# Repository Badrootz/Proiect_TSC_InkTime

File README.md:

# InkTime

## Overview

InkTime is a low-power smartwatch built around the Nordic nRF52840 SoC, designed for efficient operation, wireless connectivity, and a clean e-paper display interface. The project focuses on power optimization, modular hardware design, and practical embedded system integration.

---

## Block Diagram

```mermaid
graph TD
    Battery[LiPo Battery] --> PMIC[BQ25180 PMIC]
    PMIC --> VREG[3.3V Regulator]
    VREG --> MCU[nRF52840]

    MCU --> IMU[BMA421 IMU]
    MCU --> Display[E-Paper Display]
    MCU --> Haptic[DRV2605 Haptic Driver]
    MCU --> Fuel[MAX17048 Fuel Gauge]

    USB[USB-C] --> PMIC
    USB --> MCU

    MCU --> SWD[SWD Debug]
```

---

## Bill of Materials (BOM)

| Component      | Part Number   | Description          | Link (JLC) | Datasheet         |
| -------------- | ------------- | -------------------- | ---------- | ----------------- |
| MCU            | nRF52840-QFN  | BLE SoC              | JLC        | Nordic Datasheet  |
| PMIC           | BQ25180YBGR   | Charger + Power Path | JLC        | TI Datasheet      |
| IMU            | BMA421        | Accelerometer        | JLC        | Bosch Datasheet   |
| Fuel Gauge     | MAX17048G+T10 | Battery Monitor      | JLC        | Maxim Datasheet   |
| Haptic Driver  | DRV2605       | Vibration Driver     | JLC        | TI Datasheet      |
| Buck Converter | RT6160A       | Step-down regulator  | JLC        | Richtek Datasheet |
| USB Protection | USBLC6-2SC6   | ESD Protection       | JLC        | ST Datasheet      |
| Inductors      | Various       | Power filtering      | JLC        | Datasheets        |
| Capacitors     | Various       | Decoupling           | JLC        | Datasheets        |
| Resistors      | Various       | Pull-ups / config    | JLC        | Datasheets        |

---

## Hardware Functionality (Detailed)

### MCU (nRF52840)

Main processing unit. Handles:

* BLE communication
* Sensor data processing
* Display control
* Power management coordination

Runs at low power modes most of the time, wakes up on interrupts (IMU, buttons, timers).

---

### Power Management

#### BQ25180 PMIC

* Handles LiPo charging
* Power path management (system + battery)
* Integrated buck converter

#### RT6160 Buck Converter

* Steps voltage down efficiently to 3.3V
* Supplies MCU and peripherals

#### Power Design Notes

* Multiple decoupling capacitors placed close to ICs
* Separate analog and digital grounds where needed
* High-efficiency switching to maximize battery life

---

### IMU (BMA421)

* Connected via I2C
* Provides motion detection
* Generates interrupts for wake-up

Used for:

* Step detection
* Gesture-based wake

---

### E-Paper Display

* SPI communication
* Requires additional driving circuitry (boost + level shifting)
* Very low power (only consumes when refreshing)

Signals:

* MOSI, SCK (SPI)
* CS, DC, RST, BUSY (control)

---

### Fuel Gauge (MAX17048)

* Connected via I2C
* Monitors battery percentage
* Provides alerts when battery is low

---

### Haptic Driver (DRV2605)

* Controlled via I2C
* Drives vibration motor
* Used for notifications

---

### USB-C Interface

* Used for charging + debugging
* Includes ESD protection
* Connected to MCU USB pins

---

## nRF52840 Pin Usage

| Pin            | Function        | Reason                                   |
| -------------- | --------------- | ---------------------------------------- |
| P0.26 / P0.27  | I2C (SDA/SCL)   | Shared bus for IMU + Fuel Gauge + Haptic |
| P0.13 / P0.14  | USB D- / D+     | USB communication                        |
| P0.15 - P0.20  | SPI (Display)   | High-speed display communication         |
| P0.22 - P0.24  | Display Control | CS, DC, RST                              |
| P0.25          | Display BUSY    | Sync with display                        |
| P1.x           | GPIO            | Buttons / interrupts                     |
| P0.18          | RESET           | System reset                             |
| SWDIO / SWDCLK | Debug           | Programming                              |

Design decisions:

* I2C shared to reduce pin usage
* SPI dedicated for display performance
* Interrupt pins separated for responsiveness

---

## Power Consumption Considerations

* E-paper reduces display power drastically
* MCU spends most time in sleep (~uA consumption)
* IMU used as wake-up trigger
* Buck converter efficiency ~90%

Estimated:

* Sleep: ~20-50 µA
* Active: ~5-15 mA

---

## Gallery

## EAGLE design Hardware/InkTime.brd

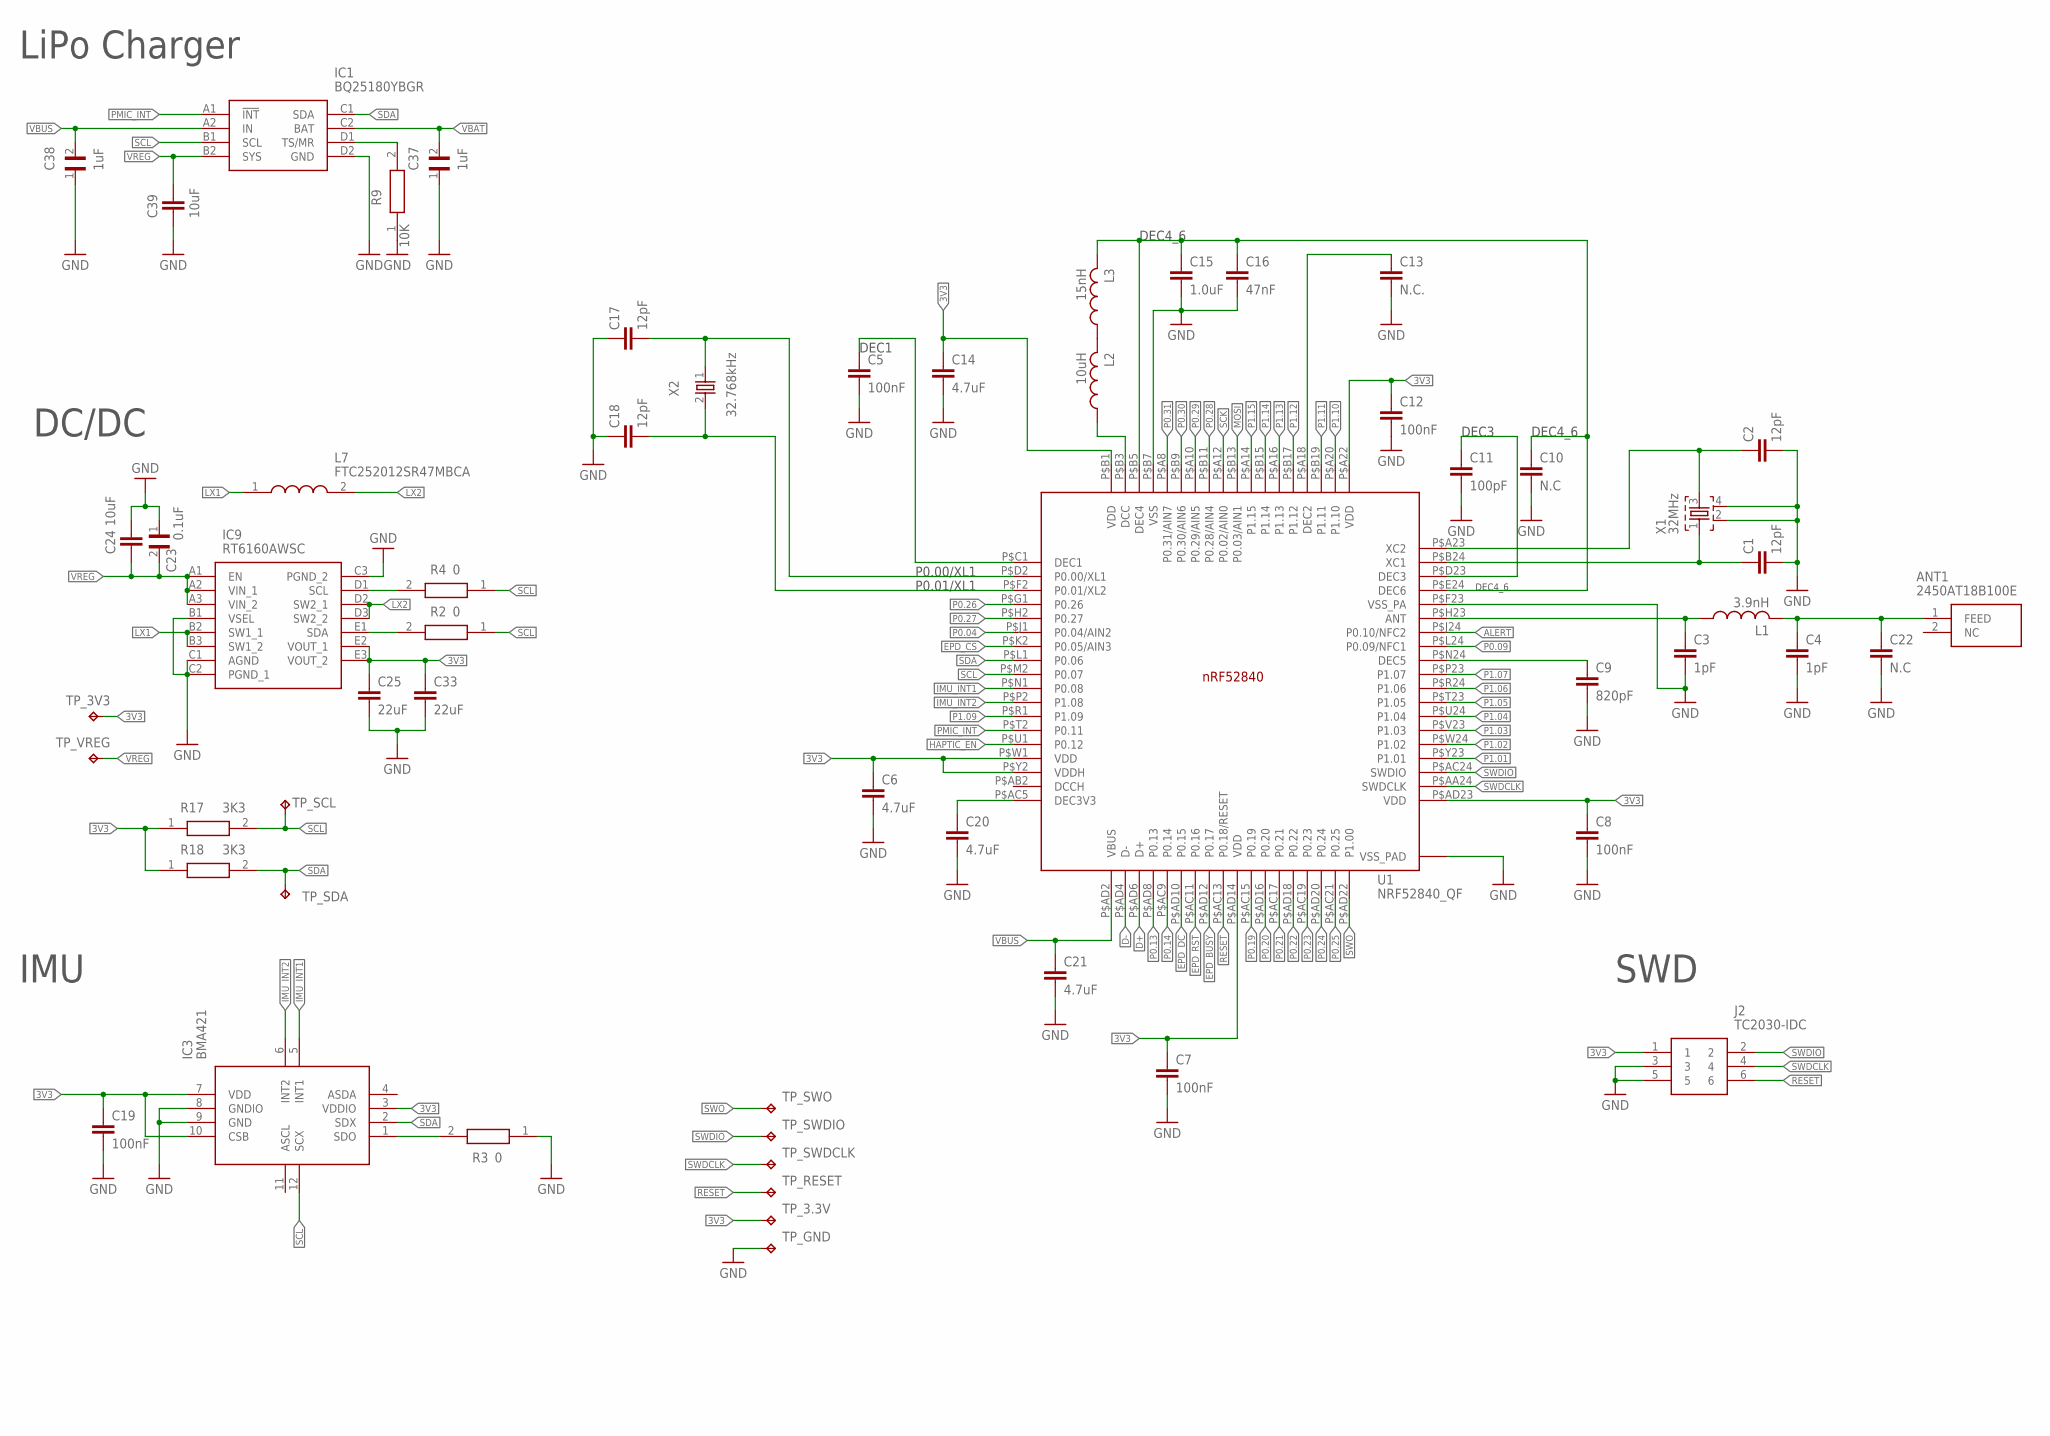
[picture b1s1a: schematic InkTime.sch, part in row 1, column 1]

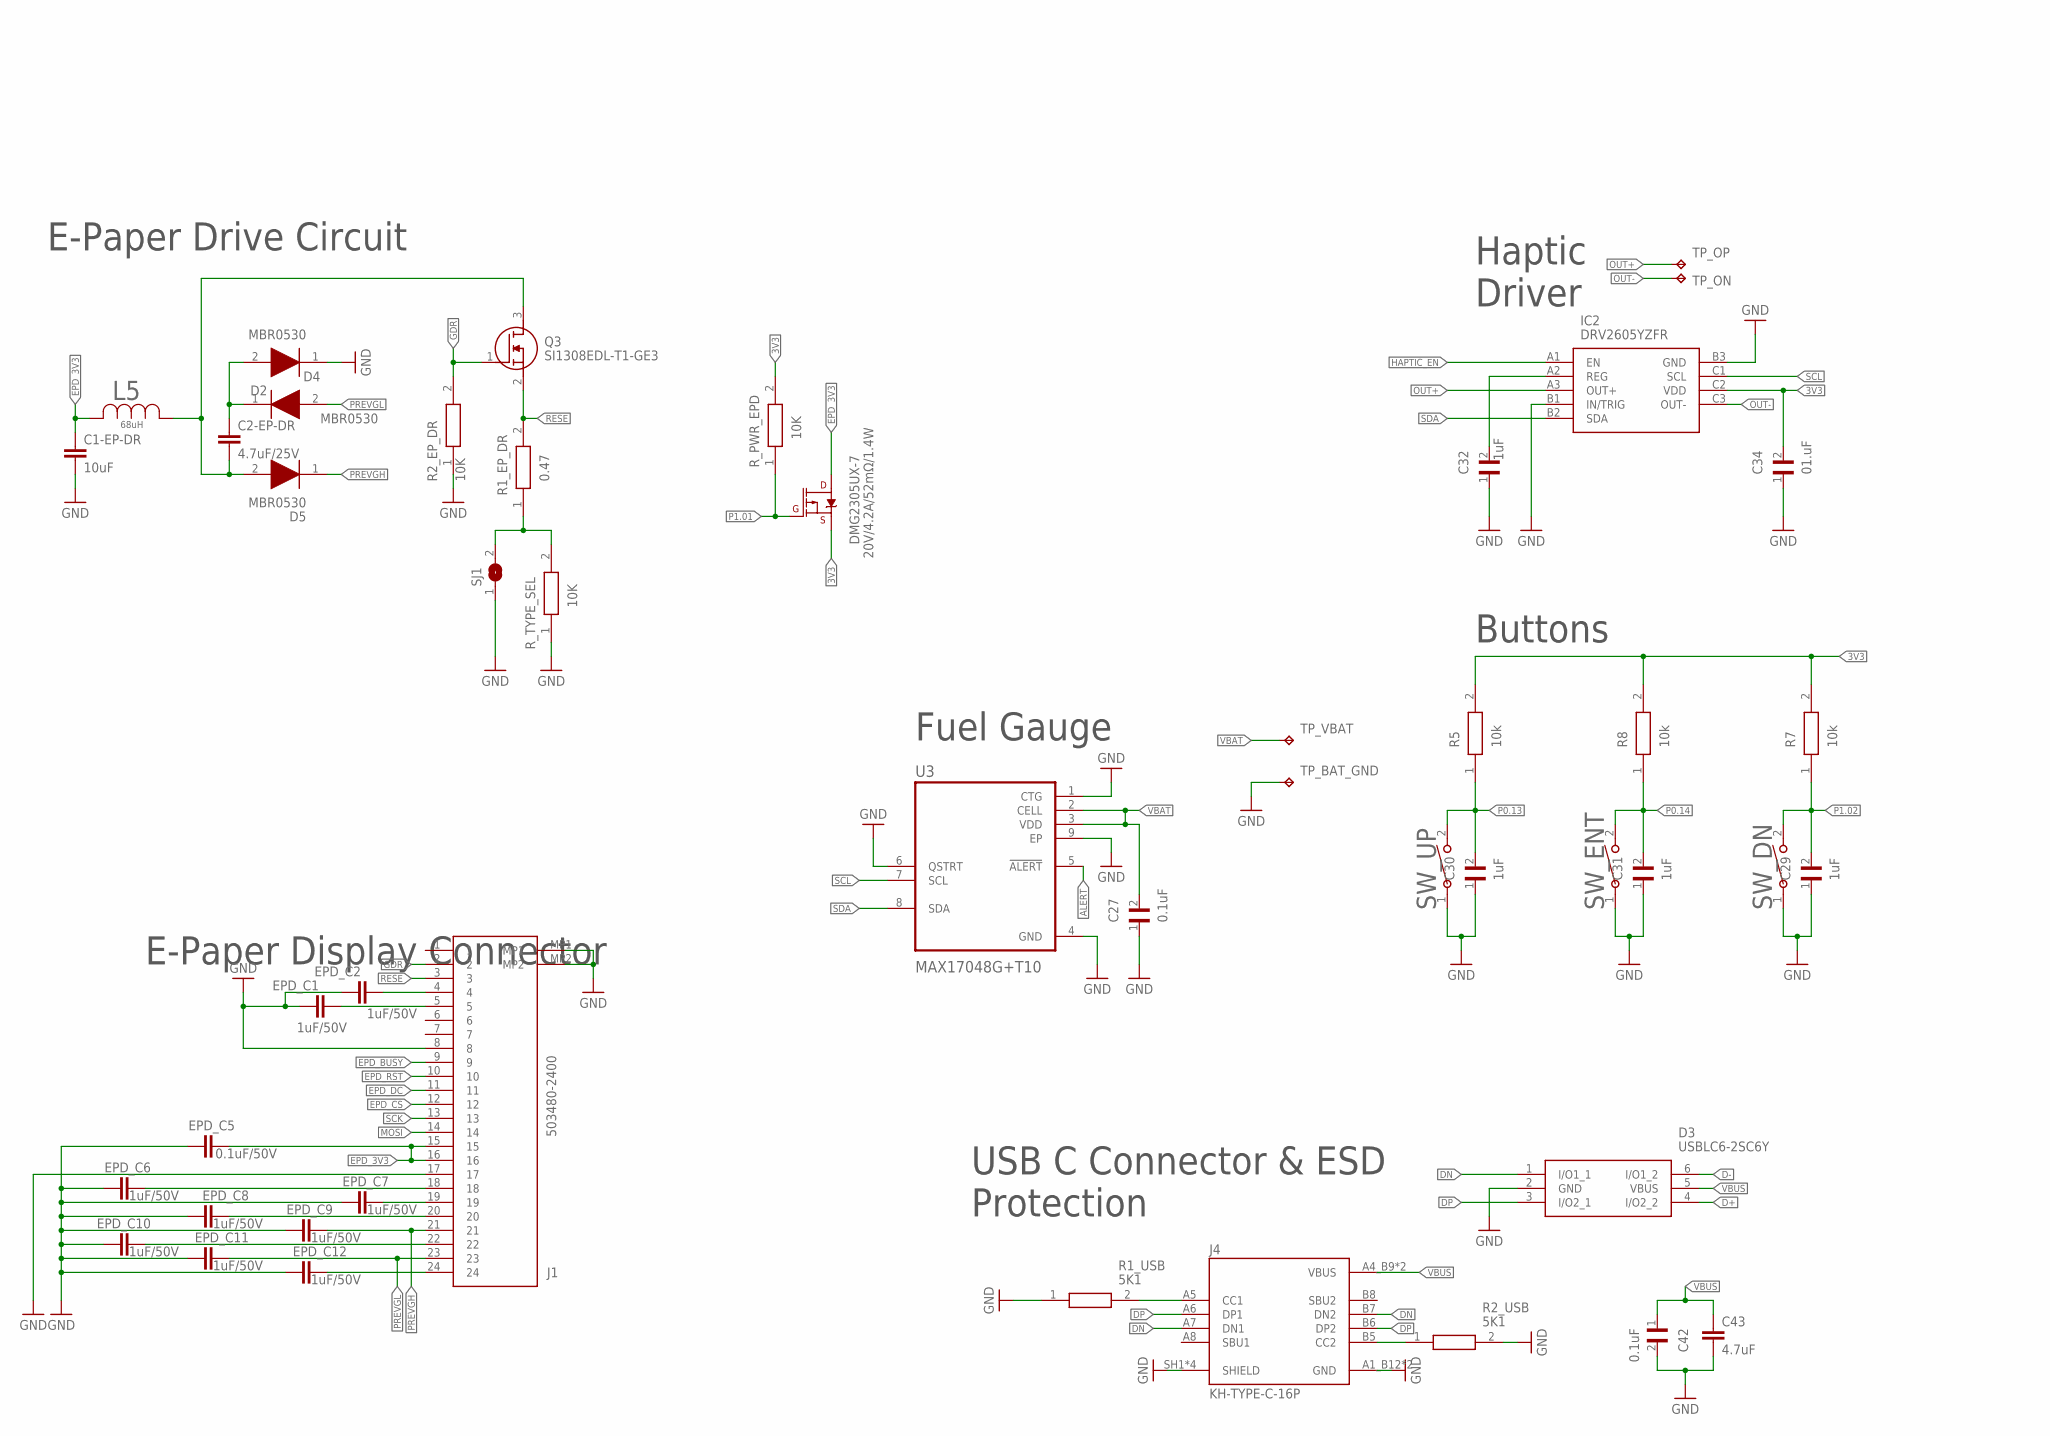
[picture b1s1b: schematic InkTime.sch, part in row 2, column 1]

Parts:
ANT1: 2450AT18B100E; 2450AT18B100E_ANTC3216X140N
C1, C2, C17, C18: 12pF; NORDIC_NRF_3_RESC0201_L
C1-EP-DR, C24, C39: 10uF; NORDIC_NRF_3_RESC0402_M
C2-EP-DR: 4.7uF/25V; NORDIC_NRF_3_RESC0402_M
C3, C4: 1pF; NORDIC_NRF_3_RESC0201_L
C5, C7, C8, C12, C19: 100nF; NORDIC_NRF_3_RESC0201_L
C6, C14, C20, C21, C43: 4.7uF; NORDIC_NRF_3_RESC0402_M
C9: 820pF; NORDIC_NRF_3_RESC0201_L
C10, C22: N.C; NORDIC_NRF_3_RESC0201_L
C11: 100pF; NORDIC_NRF_3_RESC0201_L
C13: N.C.; NORDIC_NRF_3_RESC0201_L
C15: 1.0uF; NORDIC_NRF_3_RESC0402_M
C16: 47nF; NORDIC_NRF_3_RESC0201_L
C23: 0.1uF; GRM011R60J152KE01L_2_CAPC0201X13N
C25, C33: 22uF; NORDIC_NRF_3_RESC0402_M
C27, C42: 0.1uF; GRM011R60J152KE01L_1_0201
C29, C30, C31, C32: 1uF; GRM011R60J152KE01L_1_0201
C34: 01.uF; GRM011R60J152KE01L_1_0201
C37, C38: 1uF; GRM011R60J152KE01L_2_CAPC0201X13N
D2, D4, D5: MBR0530; ESP32_C6_LIBRARY_5_SOD3716X135N
D3: USBLC6-2SC6Y; ESP32_C6_LIBRARY_3_SOT95P280X145-6N
DMG2305UX-7: 20V/4.2A/52mΩ/1.4W; ESP32_C6_LIBRARY_4_ESP32_C6_LIBRARY_4_ESP32_C6_LIBRARY_4_ES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
EPD_C1, EPD_C2, EPD_C6, EPD_C7, EPD_C8, EPD_C9, EPD_C10, EPD_C11, EPD_C12: 1uF/50V; NORDIC_NRF_3_RESC0402_M
EPD_C5: 0.1uF/50V; NORDIC_NRF_3_RESC0201_L
IC1: BQ25180YBGR; BQ25180YBGR_BGA8C40P2X4_100X155X50
IC2: DRV2605YZFR; DRV2605YZFR_BGA9C50P3X3_144X144X62
IC3: BMA421; BMA423_BMA423
IC9: RT6160AWSC; RT6160AWSC_BGA15C40P3X5_140X230X60
J1: 503480-2400; 503480-2400_5034802400
J2: TC2030-IDC; TC2030-IDC_TC2030IDC
J4: KH-TYPE-C-16P; KH-TYPE-C-16P_KINGHELM_KH-TYPE-C-16P
L1: 3.9nH; NORDIC_NRF_2_RESC0201_M
L2: 10uH; NORDIC_NRF_2_RESC0201_M
L3: 15nH; NORDIC_NRF_2_RESC0201_M
L5: 68uH; ESP32_C6_LIBRARY_2_IND_4828-WE-TPC_WRE
L7: FTC252012SR47MBCA; MLP2016SR47MT0S1_INDC2016X100N
Q3: SI1308EDL-T1-GE3; ESP32_C6_LIBRARY_6_SOT65P210X110-3N
R1_EP_DR: 0.47; ERA-1AEB3401C_0201
R1_USB, R2_USB: 5K1; ERA-1AEB3401C_0201
R2, R3, R4: 0; ERA-1AEB3401C_0201
R2_EP_DR, R9: 10K; ERA-1AEB3401C_0201
R5, R7, R8: 10k; ERA-1AEB3401C_0201
R17, R18: 3K3; ERA-1AEB3401C_0201
R_PWR_EPD: 10K; ERA-1AEB3401C_0201
R_TYPE_SEL: 10K; ERA-1AEB3401C_0201
SJ1: ESP32_C6_LIBRARY_7_JUMPER_SJ
SW_DN: 2025-10-22_07-23-44_LIBRARY_EVP-AKE31ASW_EVP-AKE3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; 2025-10-22_07-23-44_LIBRARY_SW_EVP-AKE31A_PAN
SW_ENT: 2025-10-22_07-23-44_LIBRARY_EVP-AKE31ASW_EVP-AKE3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; 2025-10-22_07-23-44_LIBRARY_SW_EVP-AKE31A_PAN
SW_UP: 2025-10-22_07-23-44_LIBRARY_EVP-AKE31ASW_EVP-AKE3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; 2025-10-22_07-23-44_LIBRARY_SW_EVP-AKE31A_PAN
TP_3.3V, TP_3V3: HECTOR_WATCH_1_TPTP20R; HECTOR_WATCH_1_TP20R
TP_BAT_GND: HECTOR_WATCH_1_TPTP20R; HECTOR_WATCH_1_TP20R
TP_GND: HECTOR_WATCH_1_TPTP20R; HECTOR_WATCH_1_TP20R
TP_ON: HECTOR_WATCH_1_TPTP20R; HECTOR_WATCH_1_TP20R
TP_OP: HECTOR_WATCH_1_TPTP20R; HECTOR_WATCH_1_TP20R
TP_RESET: HECTOR_WATCH_1_TPTP20R; HECTOR_WATCH_1_TP20R
TP_SCL: HECTOR_WATCH_1_TPTP20R; HECTOR_WATCH_1_TP20R
TP_SDA: HECTOR_WATCH_1_TPTP20R; HECTOR_WATCH_1_TP20R
TP_SWDCLK: HECTOR_WATCH_1_TPTP20R; HECTOR_WATCH_1_TP20R
TP_SWDIO: HECTOR_WATCH_1_TPTP20R; HECTOR_WATCH_1_TP20R
TP_SWO: HECTOR_WATCH_1_TPTP20R; HECTOR_WATCH_1_TP20R
TP_VBAT: HECTOR_WATCH_1_TPTP20R; HECTOR_WATCH_1_TP20R
TP_VREG: HECTOR_WATCH_1_TPTP20R; HECTOR_WATCH_1_TP20R
U1: NRF52840_QF; NORDIC_NRF_4_AQFN50P700X700X85_HS-74N
U3: MAX17048G+T10; ESP32_C6_LIBRARY_SON50P200X200X80-9N
X1: 32MHz; NORDIC_NRF_BT-XTAL_2016_N
X2: 32.768kHz; NORDIC_NRF_1_XTAL_3215_N

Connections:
3V3: C6.1, C7.1, C8.1, C12.1, C14.1, C19.1, C25.1, C33.1, C34.2, DMG2305UX-7.2 (S), IC2.C2 (VDD), IC3.3 (VDDIO), IC3.7 (VDD), IC3.10 (CSB), IC9.E2 (VOUT_1), IC9.E3 (VOUT_2), J2.1, R5.2, R7.2, R8.2, R17.1, R18.1, R_PWR_EPD.2, TP_3.3V.TP, TP_3V3.TP, U1.P$A22 (VDD), U1.P$AD14 (VDD), U1.P$AD23 (VDD), U1.P$B1 (VDD), U1.P$W1 (VDD), U1.P$Y2 (VDDH)
ALERT: U1.P$J24 (P0.10/NFC2), U3.5 (!ALERT)
D+: D3.4 (I/O2_2), U1.P$AD6 (D+)
D-: D3.6 (I/O1_2), U1.P$AD4 (D-)
DN: D3.1 (I/O1_1), J4.A7 (DN1), J4.B7 (DN2)
DP: D3.3 (I/O2_1), J4.A6 (DP1), J4.B6 (DP2)
EPD_3V3: C1-EP-DR.1, DMG2305UX-7.3 (D), EPD_C5.2, J1.15, J1.16, L5.2
EPD_BUSY: J1.9, U1.P$AD12 (P0.17)
EPD_CS: J1.12, U1.P$K2 (P0.05/AIN3)
EPD_DC: J1.11, U1.P$AD10 (P0.15)
EPD_RST: J1.10, U1.P$AC11 (P0.16)
GDR: J1.2, Q3.1 (G), R2_EP_DR.2
GND: C1.2, C1-EP-DR.2, C2.2, C3.2, C4.2, C5.2, C6.2, C7.2, C8.2, C9.2, C10.2, C11.2, C12.2, C13.2, C14.2, C15.2, C16.2, C17.1, C18.1, C19.2, C20.2, C21.2, C22.2, C23.1, C24.1, C25.2, C27.1, C29.1, C30.1, C31.1, C32.1, C33.2, C34.1, C37.1, C38.1, C39.2, C42.2, C43.2, D3.2 (GND), D4.1 (K), EPD_C1.1, EPD_C2.1, EPD_C5.1, EPD_C6.1, EPD_C7.1, EPD_C8.1, EPD_C9.1, EPD_C10.1, EPD_C11.1, EPD_C12.1, IC1.D2 (GND), IC2.B1 (IN/TRIG), IC2.B3 (GND), IC3.8 (GNDIO), IC3.9 (GND), IC9.B1 (VSEL), IC9.C1 (AGND), IC9.C2 (PGND_1), IC9.C3 (PGND_2), J1.8, J1.17, J1.MP1, J1.MP2, J2.3, J2.5, J4.A1_B12 (GND), J4.A12_B1 (GND), J4.SH1 (SHIELD), J4.SH2 (SHIELD), J4.SH3 (SHIELD), J4.SH4 (SHIELD), R1_USB.1, R2_EP_DR.1, R2_USB.2, R3.1, R9.1, R_TYPE_SEL.1, SJ1.1, SW_DN.1, SW_ENT.1, SW_UP.1, TP_BAT_GND.TP, TP_GND.TP, U1.P$74 (VSS_PAD), U1.P$75 (VSS_PAD), U1.P$76 (VSS_PAD), U1.P$77 (VSS_PAD), U1.P$78 (VSS_PAD), U1.P$79 (VSS_PAD), U1.P$80 (VSS_PAD), U1.P$81 (VSS_PAD), U1.P$82 (VSS_PAD), U1.P$83 (VSS_PAD), U1.P$84 (VSS_PAD), U1.P$85 (VSS_PAD), U1.P$86 (VSS_PAD), U1.P$87 (VSS_PAD), U1.P$88 (VSS_PAD), U1.P$89 (VSS_PAD), U1.P$90 (VSS_PAD), U1.P$B7 (VSS), U1.P$F23 (VSS_PA), U3.1 (CTG), U3.4 (GND), U3.6 (QSTRT), U3.9 (EP), X1.2, X1.4
HAPTIC_EN: IC2.A1 (EN), U1.P$U1 (P0.12)
IMU_INT1: IC3.5 (INT1), U1.P$N1 (P0.08)
IMU_INT2: IC3.6 (INT2), U1.P$P2 (P1.08)
LX1: IC9.B2 (SW1_1), IC9.B3 (SW1_2), L7.1
LX2: IC9.D2 (SW2_1), IC9.D3 (SW2_2), L7.2
MOSI: J1.14, U1.P$B13 (P0.03/AIN1)
unnamed: C9.1, U1.P$N24 (DEC5)
unnamed: IC1.D1 (TS/MR), R9.2
unnamed: IC9.D1 (SCL), R4.2
unnamed: C3.1, L1.1, U1.P$H23 (ANT)
unnamed: IC9.E1 (SDA), R2.2
unnamed: ANT1.1 (FEED), C4.1, C22.1, L1.2
unnamed: C1.1, U1.P$B24 (XC1), X1.1
unnamed: C2.1, U1.P$A23 (XC2), X1.3
unnamed: L2.1, U1.P$B3 (DCC)
unnamed: C10.1, C15.1, C16.1, L3.2, U1.P$B5 (DEC4), U1.P$E24 (DEC6)
unnamed: IC3.1 (SDO), R3.2
unnamed: C11.1, U1.P$D23 (DEC3)
unnamed: L2.2, L3.1
unnamed: C18.2, U1.P$F2 (P0.01/XL2), X2.2
unnamed: C17.2, U1.P$D2 (P0.00/XL1), X2.1
unnamed: C13.1, U1.P$A18 (DEC2)
unnamed: C5.1, U1.P$C1 (DEC1)
unnamed: C2-EP-DR.2, D5.2 (A), L5.1, Q3.3 (D)
unnamed: C2-EP-DR.1, D2.1 (K), D4.2 (A)
unnamed: R1_EP_DR.1, R_TYPE_SEL.2, SJ1.2
unnamed: EPD_C1.2, J1.5
unnamed: C32.2, IC2.A2 (REG)
unnamed: EPD_C2.2, J1.4
unnamed: EPD_C6.2, J1.18
unnamed: C20.1, U1.P$AC5 (DEC3V3)
unnamed: EPD_C7.2, J1.19
unnamed: EPD_C8.2, J1.20
unnamed: J4.B5 (CC2), R2_USB.1
unnamed: EPD_C10.2, J1.22
unnamed: J4.A5 (CC1), R1_USB.2
unnamed: EPD_C12.2, J1.24
OUT+: IC2.A3 (OUT+), TP_OP.TP
OUT-: IC2.C3 (OUT-), TP_ON.TP
P0.04: U1.P$J1 (P0.04/AIN2)
P0.09: U1.P$L24 (P0.09/NFC1)
P0.13: C30.2, R5.1, SW_UP.2, U1.P$AD8 (P0.13)
P0.14: C31.2, R8.1, SW_ENT.2, U1.P$AC9 (P0.14)
P0.19: U1.P$AC15 (P0.19)
P0.20: U1.P$AD16 (P0.20)
P0.21: U1.P$AC17 (P0.21)
P0.22: U1.P$AD18 (P0.22)
P0.23: U1.P$AC19 (P0.23)
P0.24: U1.P$AD20 (P0.24)
P0.25: U1.P$AC21 (P0.25)
P0.26: U1.P$G1 (P0.26)
P0.27: U1.P$H2 (P0.27)
P0.28: U1.P$B11 (P0.28/AIN4)
P0.29: U1.P$A10 (P0.29/AIN5)
P0.30: U1.P$B9 (P0.30/AIN6)
P0.31: U1.P$A8 (P0.31/AIN7)
P1.01: DMG2305UX-7.1 (G), R_PWR_EPD.1, U1.P$Y23 (P1.01)
P1.02: C29.2, R7.1, SW_DN.2, U1.P$W24 (P1.02)
P1.03: U1.P$V23 (P1.03)
P1.04: U1.P$U24 (P1.04)
P1.05: U1.P$T23 (P1.05)
P1.06: U1.P$R24 (P1.06)
P1.07: U1.P$P23 (P1.07)
P1.09: U1.P$R1 (P1.09)
P1.10: U1.P$A20 (P1.10)
P1.11: U1.P$B19 (P1.11)
P1.12: U1.P$B17 (P1.12)
P1.13: U1.P$A16 (P1.13)
P1.14: U1.P$B15 (P1.14)
P1.15: U1.P$A14 (P1.15)
PMIC_INT: IC1.A1 (!INT), U1.P$T2 (P0.11)
PREVGH: D5.1 (K), EPD_C9.2, J1.21
PREVGL: D2.2 (A), EPD_C11.2, J1.23
RESE: J1.3, Q3.2 (S), R1_EP_DR.2
RESET: J2.6, TP_RESET.TP, U1.P$AC13 (P0.18/RESET)
SCK: J1.13, U1.P$A12 (P0.02/AIN0)
SCL: IC1.B1 (SCL), IC2.C1 (SCL), IC3.12 (SCX), R2.1, R4.1, R17.2, TP_SCL.TP, U1.P$M2 (P0.07), U3.7 (SCL)
SDA: IC1.C1 (SDA), IC2.B2 (SDA), IC3.2 (SDX), R18.2, TP_SDA.TP, U1.P$L1 (P0.06), U3.8 (SDA)
SWDCLK: J2.4, TP_SWDCLK.TP, U1.P$AA24 (SWDCLK)
SWDIO: J2.2, TP_SWDIO.TP, U1.P$AC24 (SWDIO)
SWO: TP_SWO.TP, U1.P$AD22 (P1.00)
VBAT: C27.2, C37.2, IC1.C2 (BAT), TP_VBAT.TP, U3.2 (CELL), U3.3 (VDD)
VBUS: C21.1, C38.2, C42.1, C43.1, D3.5 (VBUS), IC1.A2 (IN), J4.A4_B9 (VBUS), J4.A9_B4 (VBUS), U1.P$AD2 (VBUS)
VREG: C23.2, C24.2, C39.1, IC1.B2 (SYS), IC9.A1 (EN), IC9.A2 (VIN_1), IC9.A3 (VIN_2), TP_VREG.TP

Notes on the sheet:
LiPo Charger
DC/DC
IMU
DEC4_6
DEC3
DEC1
P0.00/XL1
P0.01/XL1
SWD
Haptic Driver
Buttons
USB C Connector & ESD Protection
E-Paper Drive Circuit
E-Paper Display Connector
Fuel Gauge

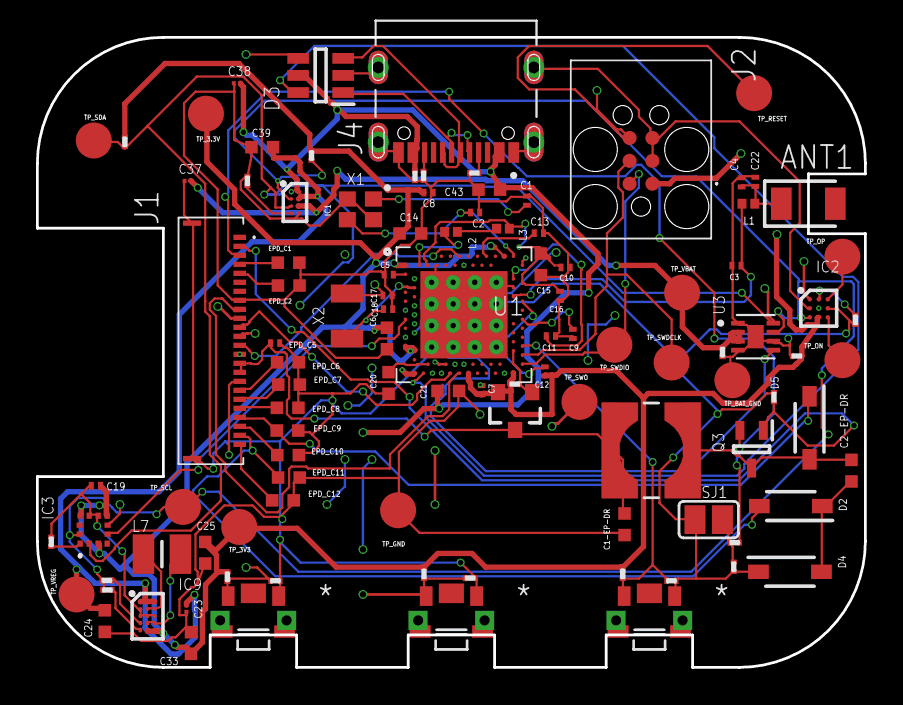
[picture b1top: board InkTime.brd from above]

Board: 4 copper layers, 46.0 x 35.0 mm, 105 parts (0 on the bottom side), 70 nets.

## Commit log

2026-04-10 Structura proiectului
2026-04-10 Structura proiect 2.0
2026-04-22 Rezolvare issues
2026-04-22 adaugat readme

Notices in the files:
parts and their libraries:
COPYRIGHT: Copyright (C) 2024 Ultra Librarian. All rights reserved.
COPYRIGHT: Copyright (C) 2025 Ultra Librarian. All rights reserved.
